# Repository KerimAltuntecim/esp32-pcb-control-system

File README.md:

# ESP32 PCB Control System

**English summary:** ESP32-C3 based control PCB prototype with Nextion HMI, stepper, sensor, relay, triac and MOSFET interfaces. The repository documents the hardware and firmware structure; it is not a production-certified design.

ESP32-C3 tabanlı, Nextion HMI ekran üzerinden kontrol edilen çok işlevli bir PCB prototipi. Kart; sensör okuma, motor sürme, röle/triyak/MOSFET çıkışları ve kullanıcı arayüzü haberleşmesini tek bir donanım üzerinde birleştirir.

## Öne çıkan özellikler

- ESP32-C3-WROOM-02 mikrodenetleyici
- Nextion ekran ile UART haberleşmesi
- STEP/DIR sinyalleriyle A4988 step motor sürücüsü
- PC817 optokuplörlü sensör ve MOSFET kontrol girişleri
- MOC3022M + BTA136-500 triyak sürücü katı
- Röle ile harici yük açma/kapama
- IR2101 + IRF540N MOSFET güç sürücü katı
- TCRT5000 dijital sensör girişi
- LM35 analog sıcaklık girişi
- RGB LED PWM kontrolü ve buzzer uyarısı
- 15 V'tan 5 V üreten L7805 besleme katı

## Nextion arayüzü

Nextion ekran üzerinden aşağıdaki menüler tasarlanmıştır:

- Step motor: yön ve adım miktarı
- Triyak: kontrol/ateşleme seviyesi
- RGB LED: kırmızı, yeşil ve mavi parlaklık seviyeleri
- Sensör: algılama görseli ve 0/1 durumu
- MOSFET: PWM kontrol seviyesi
- Röle: açma/kapama

ESP32 firmware’i Nextion’dan gelen `role`, `tri`, `fet`, `rgbr`, `rgbg`, `rgbb`, `sens` ve `step` komutlarını işler. `kerim.HMI`, arayüzün düzenlenebilir Nextion Editor kaynak dosyasıdır.

## Depo içeriği

GitHub web yüklemesi nedeniyle dosyalar depo kökünde açıklayıcı öneklerle tutulur:

- `firmware__...`: ESP32 Arduino firmware’i
- `hardware__...`: KiCad şematik, PCB ve proje dosyaları
- `nextion__...`: Nextion HMI kaynak dosyası
- `image__...`: PCB, şematik ve arayüz görselleri

## Doğrulama ve gelecek geliştirmeler

- UART komut akışı ve HMI menüleri yazılım incelemesiyle doğrulanmıştır.
- Donanımın tüm çalışma senaryoları bu sürümde yeniden test edilmemiştir.
- Sonraki adımlar: gerçek yük testleri, akım/ısı ölçümleri, koruma elemanlarının gözden geçirilmesi, sıfır geçiş kontrollü triyak sürme ve üretim öncesi PCB doğrulaması.

## Prototip durumu ve sınırlamalar

Bu çalışma ilk el montajı yapılmış bir prototiptir; seri üretime hazır ürün olarak değerlendirilmemelidir. Firmware’in bazı bölümleri donanım üzerinde yeniden doğrulanmalıdır. Triyak ve MOSFET kontrol seviyelerinin gerçek yükteki etkisi, bağlı yük tipine ve güç katı ayarlarına bağlıdır. Batarya ADC ölçümü bu firmware sürümünde aktif bir özellik olarak kullanılmamaktadır.

Triyak/röle tarafında şebeke gerilimi bulunabileceğinden test ve kullanım sırasında uygun elektriksel izolasyon ve güvenlik prosedürleri uygulanmalıdır.

## Lisans

MIT License ile yayımlanmıştır.

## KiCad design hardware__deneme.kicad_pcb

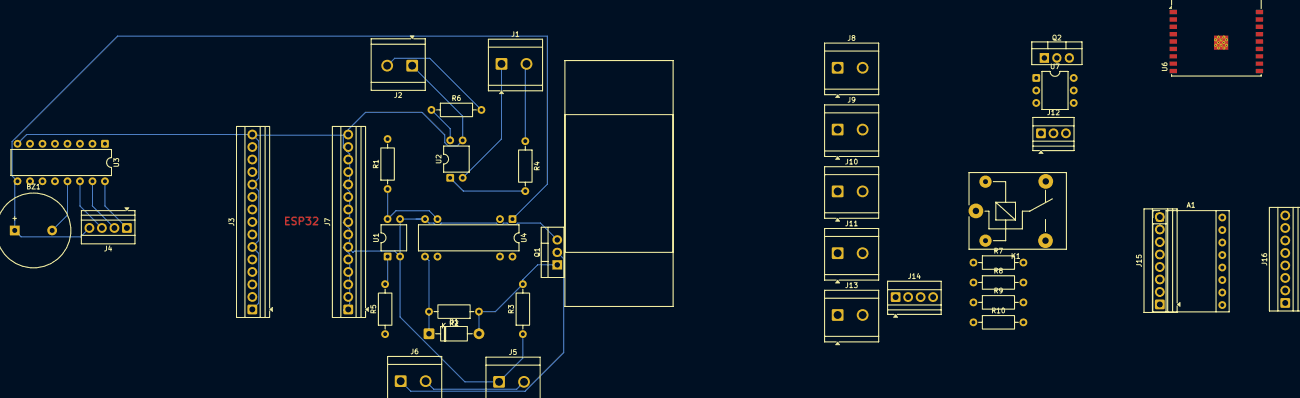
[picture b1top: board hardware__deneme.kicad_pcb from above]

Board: 2 copper layers, 38 parts (0 on the bottom side), 38 nets.

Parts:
A1: Pololu_Breakout_A4988; Pololu_Breakout-16_15.2x20.3mm
BZ1: Buzzer; Buzzer_15x7.5RM7.6
D1: 1N4007; D_DO-41_SOD81_P10.16mm_Horizontal
J1, J2, J5, J6: Screw_Terminal_01x02; TerminalBlock_CUI_TB007-508-02_1x02_P5.08mm_Horizontal
J3, J7: Screw_Terminal_01x15; TerminalBlock_Xinya_XY308-2.54-15P_1x15_P2.54mm_Horizontal
J4, J14: Screw_Terminal_01x04; TerminalBlock_Xinya_XY308-2.54-4P_1x04_P2.54mm_Horizontal
J8, J11: lamba; TerminalBlock_CUI_TB007-508-02_1x02_P5.08mm_Horizontal
J9, J10: şebeke; TerminalBlock_CUI_TB007-508-02_1x02_P5.08mm_Horizontal
J12: Screw_Terminal_01x03; TerminalBlock_Xinya_XY308-2.54-3P_1x03_P2.54mm_Horizontal
J13: batarya; TerminalBlock_CUI_TB007-508-02_1x02_P5.08mm_Horizontal
J15, J16: Screw_Terminal_01x08; TerminalBlock_Xinya_XY308-2.54-8P_1x08_P2.54mm_Horizontal
K1: SANYOU_SRD_Form_C; Relay_SPDT_SANYOU_SRD_Series_Form_C
Q1: IRF540N; TO-220-3_Vertical
Q2: BT136-500; TO-220-3_Vertical
R1, R4, R5, R6, R7: 670; R_Axial_DIN0207_L6.3mm_D2.5mm_P10.16mm_Horizontal
R2: 22; R_Axial_DIN0207_L6.3mm_D2.5mm_P10.16mm_Horizontal
R3: 10k; R_Axial_DIN0207_L6.3mm_D2.5mm_P10.16mm_Horizontal
R8: 220; R_Axial_DIN0207_L6.3mm_D2.5mm_P10.16mm_Horizontal
R9: 170k; R_Axial_DIN0207_L6.3mm_D2.5mm_P10.16mm_Horizontal
R10: 330k; R_Axial_DIN0207_L6.3mm_D2.5mm_P10.16mm_Horizontal
U1, U2: PC817; DIP-4_W7.62mm
U3: ULN2003; DIP-16_W7.62mm
U4: IR2103; DIP-8-16_W7.62mm
U6: ESP32-C3-WROOM-02
U7: MOC3022M; DIP-6_W7.62mm

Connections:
+3.3V: J2.2, R6.2
+15V: A1.8 (VMOT), BZ1.1 (+), J4.4, K1.2, U3.9 (COM), U4.1 (VCC)
/3.3V: A1.2 (VDD), J3.13, J3.14
/5V: J3.2, J3.3
/MOSFET: R5.1, U6.4 (IO5)
/blue: J4.1, U3.16 (O1)
/buzzer: BZ1.2 (-), U3.13 (O4)
/green: J4.3, U3.14 (O3)
/lm35: J12.2, U6.16 (IO2)
/red: J4.2, U3.15 (O2)
/röle: K1.5, U3.12 (O5)
/sens: R6.1, U2.4, U6.3 (IO4)
/ölçüm: R9.2, R10.1, U6.18 (IO0)
GND: A1.1 (GND), A1.7 (GND), J2.1, J3.1, J3.6, J3.11, J3.15, J5.1, J7.1, J7.6, J7.8, J7.11, J7.14, J7.15, J13.1, Q1.3 (S), R3.1, R10.2, U1.2, U1.3, U2.3, U3.8 (GND), U4.4 (COM), U7.2
unnamed: A1.4 (1A), J14.2
unnamed: A1.3 (1B), J14.1
unnamed: A1.5 (2A), J14.3
unnamed: A1.6 (2B), J14.4
unnamed: A1.13 (~RESET), A1.14 (~SLEEP)
unnamed: D1.2 (A), Q1.1 (G), R2.1, R3.2
unnamed: D1.1 (K), R2.2, U4.5 (LO)
unnamed: J1.1, U2.2
unnamed: J1.2, R4.1
unnamed: J5.2, J6.2
unnamed: J6.1, Q1.2 (D)
unnamed: J8.1, Q2.2 (A2), U7.6
unnamed: J8.2, J9.1
unnamed: J9.2, Q2.1 (A1), R7.1
unnamed: J10.1, K1.3
unnamed: J10.2, J11.1
unnamed: J11.2, K1.1
unnamed: J13.2, R9.1
unnamed: R4.2, U2.1
unnamed: R5.2, U1.1
unnamed: R7.2, U7.4
unnamed: R8.1, U7.1
unnamed: R1.1, U1.4, U4.3 (~LIN)
unnamed: U6.9 (GND), U6.19 (GND)
